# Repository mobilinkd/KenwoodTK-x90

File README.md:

Please view the Jupyter Notebook [here](https://nbviewer.jupyter.org/github/mobilinkd/KenwoodTK-x90/blob/master/Kenwood_TK-790.ipynb).

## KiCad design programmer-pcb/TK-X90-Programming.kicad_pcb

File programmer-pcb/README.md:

# Kenwood TK-x90 Programmer PCB

This directory contains the KiCad project for the Kenwood TK-x90 programmer.
This is designed to adapt a standard 5V capable USB to serial UART adapter
to the one-wire serial protocol used by the Kenwood TK-690, TK-790 and
TK-890 radios.  It is intended to be used with the TK-x90 programmer
connector in this repository.

<table>
  <tr>
    <td>  </td>
  </tr>
</table>

## License

This circuit design is licensed under the [CC-BY-SA](http://creativecommons.org/licenses/by-sa/4.0/).

Please attribute the work to *Rob Riggs, WX9O, Mobilinkd LLC*.

## Schematic

<table>
  <tr>
    <td>  </td>
  </tr>
</table>

## Theory of Operation

This circuit converts a standard 3-wire serial interface into a one-wire serial
interface, ensuring the data transmitted by the serial two-wire interface does
not see its TX data on the RX line (no local echo).

One side of the interface has GND, TX and RX.  The other side has GND and TRD
(transmit/receive data).  TRD is pulled high by the radio when powered on.

The input to the programmer is a standard 3-wire asynchronous serial connection
from a 5V capable USB to TTL serial adapter.  This is converted to a one-wire
serial protocol.  Unlike the one-wire implementation in Motorola radios, the
Kenwood protocol does not allow local echo of the transmitted data.

The serial RX line is pulled high and serial TX operates in push-pull mode. 

The N-channel MOSFET Q1 shuts off the RX connection when TX brings the line
LOW.  This leave RX high while the serial module transmits. TX pulls TRD low
via D1. TX operates as if in open drain mode.

When the radio is transmitting, TX is high, Q1 is conducting, allowing TRD to
pull RX high or low through Q1.  D1 prevents the TX line from interfering
the TRD data transmission.

It might be helpful to note that there is a 100Ω resistor on the TRD line in
the radio itself.

## BOM

<table>
  <tr>
    <td>  </td>
  </tr>
</table>

 1. 2x [MillMax 310-13-101-41-001000](https://www.digikey.com/product-detail/en/mill-max-manufacturing-corp/310-13-101-41-001000/ED7464-01-ND/265808)
 1. 1x [2N7002](https://www.digikey.com/product-detail/en/on-semiconductor/2N7002/2N7002NCT-ND/244664) SOT-23 N-Channel MOSFET
 1. 1x [MMBD4148](https://www.digikey.com/product-detail/en/diodes-incorporated/MMBD4148-7-F/MMBD4148-FDICT-ND/815711) SOT-23 General Purpose Diode
 1. 1x 100kΩ Resistor, 0603 (1608 Metric) package
 1. 1x 1kΩ Resistor, 0603 (1608 Metric) pacakge
 1. 1x 220Ω Resistor, 0603 (1608 Metric) pacakge
 1. 1x [USB to serial adapter](https://www.digikey.com/product-detail/en/seeed-technology-co-ltd/317990279/1597-1492-ND/7056809), 5V tolerant (not shown above).
 1. Lenth of CAT 5e Ethernet cable (any round, 5mm diameter Ethernet cable will do).
 1. Shink tubing that will fit over the Ethernet cable.  Otherwise electrical tape will work.

The MillMax parts are usually cheaper to order in longer strips.  They are
designed to fit IC leads, useful for making custom IC sockets.  Rather than
just buying two, consider buying one or more [strips of 64](https://www.digikey.com/products/en?keywords=310-13-164-41-001000).
If you intend to make the microphone adapter, you will need 8 more.

I used a CP2102-based board similar to the one linked above, but without the
pin headers attached.  I found these on eBay for about 5 for $10.

## Assembly

Mount the surface mount components on the PCB.  I used solder paste in a
syringe applied to the pads and reflowed the board in an oven.  But these
should be reasonable sized components to hand solder using a soldering
iron.  Space is constrained in the plug for this board so we
could not use larger parts or through-hold components.

Once the surface mount components are soldered in place, solder the pads
P1 and P2 in place on the botton of the board.  Keep the oriention as
close to the silkscreen orientation as possible.

## Cable Assembly

These assembly instruction assume that you have the [connector components](../programmer-connector/README.md)
completed and partially assembled.

 1. Cut an the Ethernet cable to the desired length.
 1. Cut off any RJ-45 connectors that are attached at either end.
 1. Cut back about 10-15mm of the outer insulation from one end.
 1. Find the blue/white, orange, and the orange/white wires.
 1. Strip about 3-4mm of insulation from these three wires.
 1. Trim the remaining wires back to the outer insulation, leaving just
    these three exposed.
 1. Slide the shrink tubing onto the cable.
 1. Solder the blue/white wire to GND on the USB/serial board.
 1. Solder the orange wire to the TX line of the USB/serial board.
 1. Solder the orange/white wire to the RX line of the USB/serial board.
 
One half of the cable is complete.  Verify that the shrink tubing is on
cable.  We won't heat the shrink tubing until we verify the cable works.
 
We now turn our attention to the other end of the cable and the  PCB
that was assembled above.  Note that when soldering the serial wires,
we are **not crossing the TX/RX wires**.
 
Before we begin, there may be burrs or other protrusions on the PCB from
manufacturing.  These need to be filed off smooth so that the PCB will fit
in the connector base.  Clean up the PCB and verify that it will in the
base, but do not push it in so far that it engages the clips.  The board
diameter should measure 17mm.  There is only 0.5mm clearance for the PCB
designed into the connector assembly.
 
 1. Slide the connector shell/boot assembly over the end of the cable.
 1. Cut back about 15mm of the outer insulation from the remaining end.
 1. Find the blue/white, orange, and the orange/white wires.
 1. Strip about 3-4mm of insulation from these three wires.
 1. Trim the remaining wires back to the outer insulation, leaving just
    these three exposed.
 1. Solder the blue/white wire to GND on the PCB.
 1. Solder the orange wire to the TX line of the PCB.
 1. Solder the orange/white wire to the RX line of PCB.

The cable ends have been soldered.  We are now going to mount the PCB
in the connector base and verify that the cable works.

 1. Orient the PCB so that the two MillMax sockets are near the screw
    attachement point of the base.
 1. Find the clips and align the slots on the PCB with the clips.
 1. Push the PCB into the base until the clips engage.
 
Now we need to test the programmer cable.  I recommend going through the
full read and write process with the Kenwood programming software.
Information on how to do that is outside the scope of this brief
document.

In a pinch we can just watch the traffic come through as the radio
boots up, testing reading only.  This is what we will do here.

A word of warning/advice.  Do not connect or disconnect the cable
with the radio on.  Do not power on the radio if the cable is connected
to the radio but not plugged in to a USB port.

 1. Ensure the radio is powered off.
 1. Connect the serial adapter to a computer.
 1. Connect the adapter to the radio, aligning the connector base with the
    PCB carefully and screwing in the connector to ensure that it is
    properly secured.
 1. Open a serial console (such as PuTTY or CuteCom)
 1. Set the serial parameters to 9600 baud, 8N1.
 1. Open the serial port.
 1. Turn on the radio.
 1. You should see a bunch of binary data flow into the terminal
 1. Turn the channel select knob on the radio.  You should see data being
    emitted for each click of the knob.

If this test failed, go back and verify all of the connections.  Verify
that the USB/Serial adapter did not reverse the TX/RX designation on the
adapter board.  (That has bitten me more than once.)

Assuming it passed, we need to finish the assembly.

 1. Turn the radio off.
 1. Disconnect the cable from the radio.
 1. Unplug the USB serial adapter.
 1. Use the shink tubing or electrical tape to protect the connection to
    the USB Serial adapter.
 1. Slide the connector boot assembly down towards the base.
 1. Orient the boot assembly so the cutouts line up with the clips holding
    the PCB in place.  This should also orient the clips on the shell with
    the cutouts on the base.
 1. Insert the shell into the base, pressing until the clips lock in place.
    This may require some force.

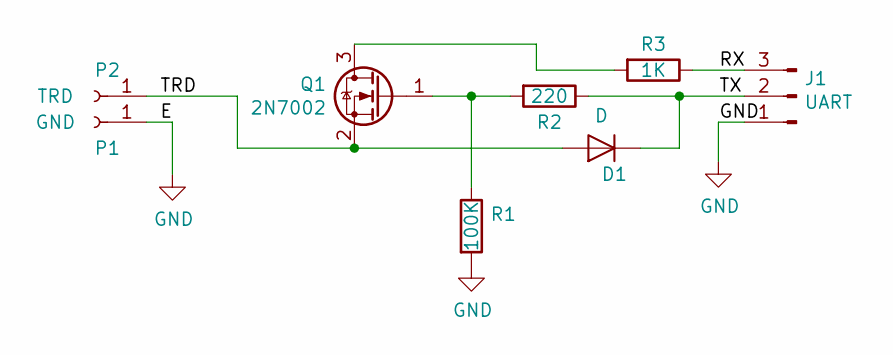
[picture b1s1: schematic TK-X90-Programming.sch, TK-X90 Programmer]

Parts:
D1: D; SOT-23
J1: UART; PinHeader_1x03_P2.54mm_Vertical
P1: GND; PinSocket_1x01_P2.54mm_Vertical
P2: TRD; PinSocket_1x01_P2.54mm_Vertical
Q1: 2N7002; SOT-23
R1: 100K; R_0603_1608Metric
R2: 220; R_0603_1608Metric
R3: 1K; R_0603_1608Metric

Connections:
/RX: J1.3, R3.1
/TRD: D1.1 (A), P2.1, Q1.2 (S)
/TX: D1.3 (K), J1.2, R2.1
GND: J1.1, P1.1, R1.2
unnamed: Q1.1 (G), R1.1, R2.2
unnamed: Q1.3 (D), R3.2

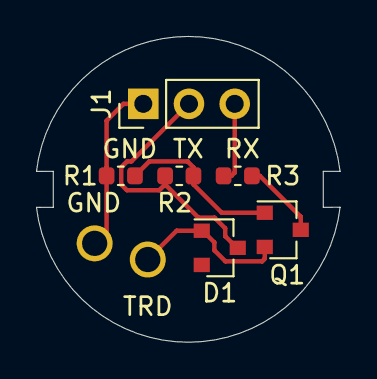
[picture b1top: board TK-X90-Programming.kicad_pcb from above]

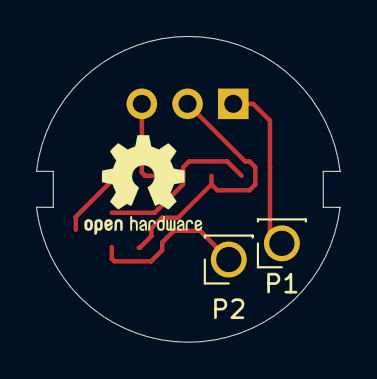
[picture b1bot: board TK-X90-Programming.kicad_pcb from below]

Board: 2 copper layers, 16.9 x 17.0 mm, 8 parts (2 on the bottom side), 6 nets.

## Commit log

2020-04-08 Initial commit.
2020-04-08 Reduce voids in strain relief to aid in printability.
2020-04-12 Update programmer models. Add README.md file.
2020-04-12 Fix bogus image link.
2020-04-12 Fix image size.
2020-04-12 Update documentation and part orientation.
2020-04-12 Add PCB images and README.md with theory of operation, BOM and build instructions.
2020-04-13 Update documentation.
2020-04-27 Add microphone connector housing. This should work for both programmer and microphone PCBs. Includes a jig to help hold & orient Mill-Max parts when building PCBs.
2020-04-30 Update connector base to increase size of cutouts.
2020-06-30 Add details and images on head units.
2020-07-08 Add power on sequence and ignition sense info.
2020-07-09 Add programmer adapter and programmer circuit.
2020-07-09 Add README.md to direct people to the notebook.
2020-07-10 Fix $ mathjax corruption.
2020-07-10 Reduce connector image size.
2020-07-27 Update the notebook. Add remaining items.
2020-07-27 Minor edit.
2020-07-27 Add link to SM50 work.
2020-07-27 Add missing USB device name.
2020-07-27 Fix type.
2020-07-29 Add information about the microcontroller. Remove redundant material. Minor edits.
2021-08-30 Remove redundant text.

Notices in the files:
programmer-pcb/TK-X90-Programming.kicad_pcb:
CC BY-SA 2.0
© 2020 Mobilinkd LLC
programmer-pcb/TK-X90-Programming.sch:
https://creativecommons.org/licenses/by-sa/2.0
